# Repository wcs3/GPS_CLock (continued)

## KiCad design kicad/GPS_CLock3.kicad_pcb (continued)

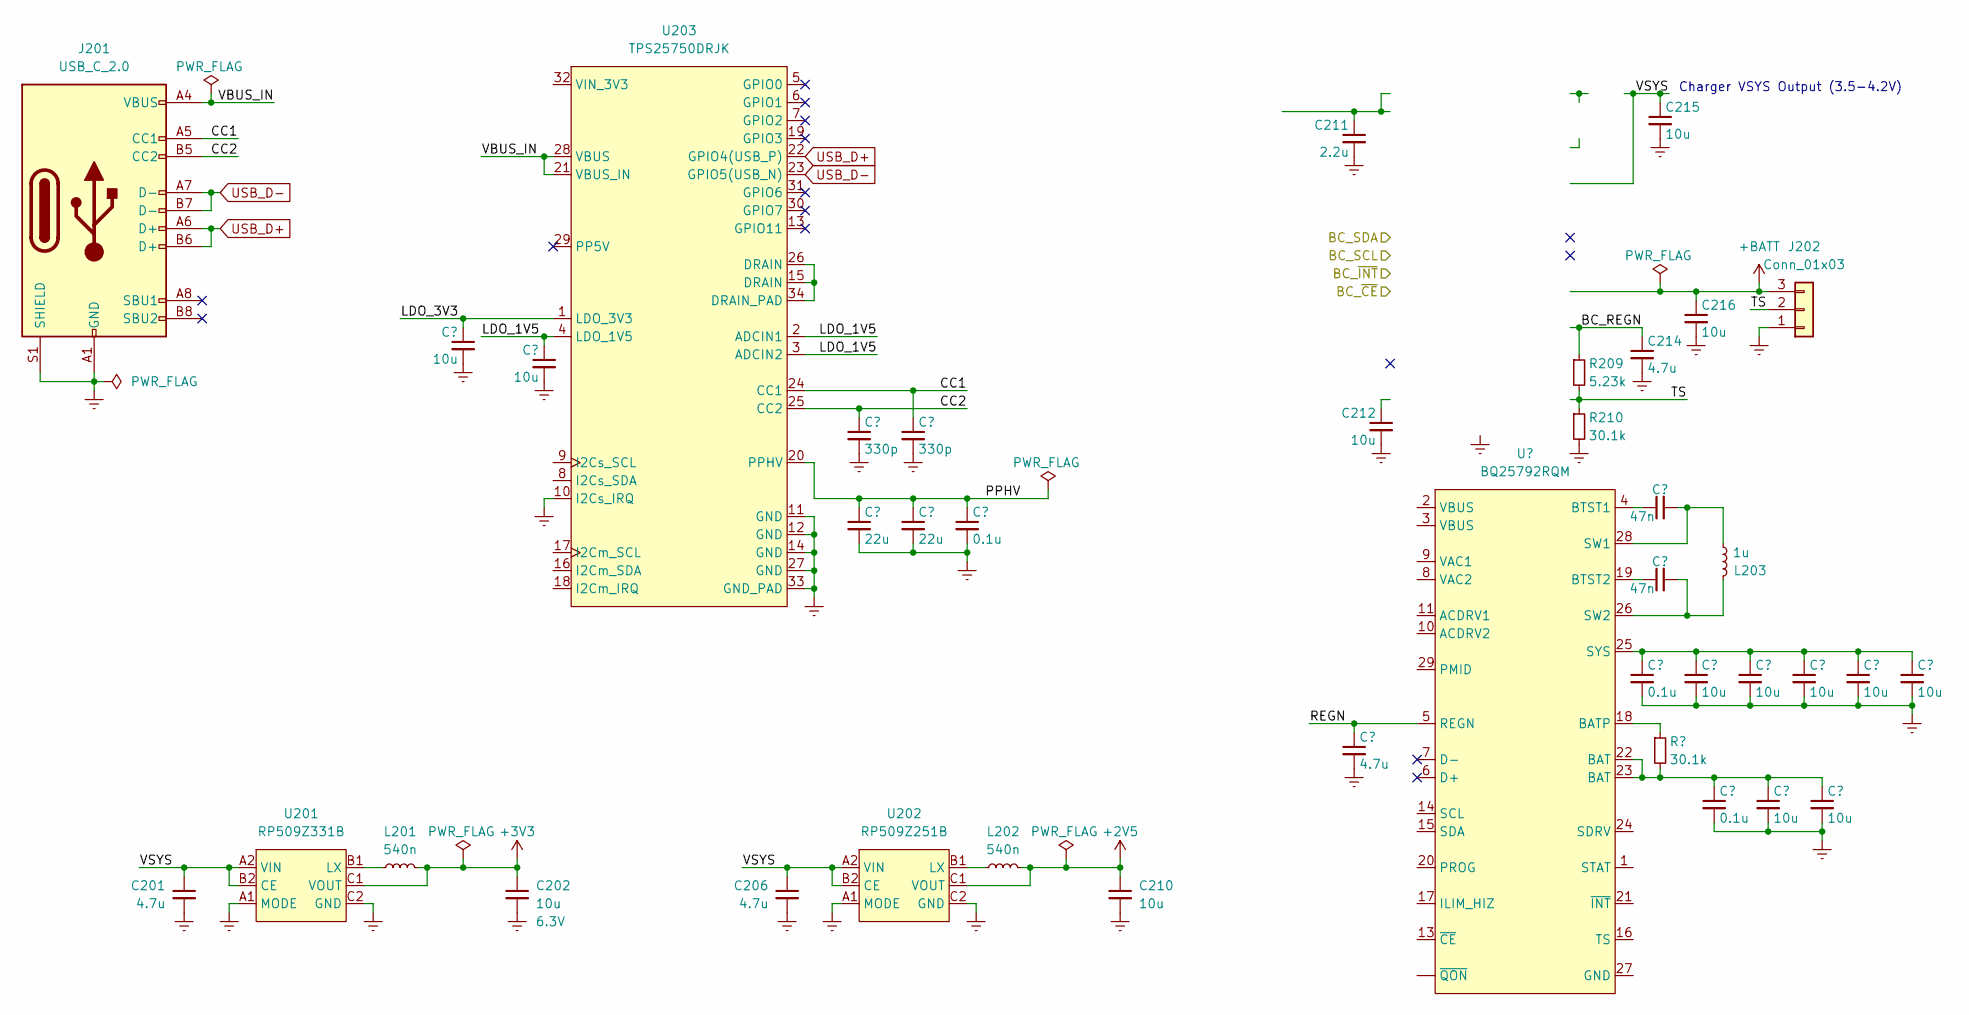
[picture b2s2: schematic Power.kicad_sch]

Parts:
C201, C206, C214: 4.7u; C_0402_1005Metric
C202: 10u; C_0402_1005Metric; Voltage 6.3V
C210, C212, C215, C216: 10u; C_0402_1005Metric
C211: 2.2u; C_0603_1608Metric
J201: USB_C_2.0; USB_C_Receptacle_JAE_DX07S016JA1R1500
J202: Conn_01x03; JST_XH_B3B-XH-A_1x03_P2.50mm_Vertical
L201, L202: 540n; L_0805_2012Metric
L203: 1u; Bourns_SRP2512
R209: 5.23k; R_0402_1005Metric
R210: 30.1k; R_0402_1005Metric
U201: RP509Z331B; WLCSP-6_1.4x1.0mm_P0.4mm
U202: RP509Z251B; WLCSP-6_1.4x1.0mm_P0.4mm
U203: TPS25750DRJK; POWERWQFN-40

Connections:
+2V5: C210.1, L202.2, U202.C1 (VOUT); also elsewhere on the board
+3V3: C202.1, L201.2, U201.C1 (VOUT); also elsewhere on the board
+BATT: C216.1, J202.3; also elsewhere on the board
/Power/BC_REGN: C214.1, R209.1; also elsewhere on the board
/Power/CC1: J201.A5 (CC1), U203.24 (CC1)
/Power/CC2: J201.B5 (CC2), U203.25 (CC2)
/Power/TS: J202.2, R209.2, R210.1; also elsewhere on the board
/Power/VBUS_IN: J201.A4 (VBUS), J201.A9 (VBUS), J201.B4 (VBUS), J201.B9 (VBUS), U203.21 (VBUS_IN), U203.28 (VBUS)
/Power/VBUS_OUT: C211.1; also elsewhere on the board
/Power/VSYS: C201.1, C206.1, C215.1, L203.2, U201.A2 (VIN), U201.B2 (CE), U202.A2 (VIN), U202.B2 (CE); also elsewhere on the board
Earth: C201.2, C202.2, C206.2, C210.2, C211.2, C212.2, C214.2, C215.2, C216.2, J201.A1 (GND), J201.A12 (GND), J201.B1 (GND), J201.B12 (GND), J201.S1 (SHIELD), J202.1, R210.2, U201.A1 (MODE), U201.C2 (GND), U202.A1 (MODE), U202.C2 (GND); also elsewhere on the board
unnamed 277: C212.1; also elsewhere on the board
unnamed 278: L203.1; also elsewhere on the board
unnamed: L201.1, U201.B1 (LX)
unnamed: L202.1, U202.B1 (LX)
USB_D+: J201.A6 (D+), J201.B6 (D+), U203.22 (GPIO4(USB_P)); also elsewhere on the board
USB_D-: J201.A7 (D-), J201.B7 (D-), U203.23 (GPIO5(USB_N)); also elsewhere on the board

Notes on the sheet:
Charger VSYS Output (3.5-4.2V)

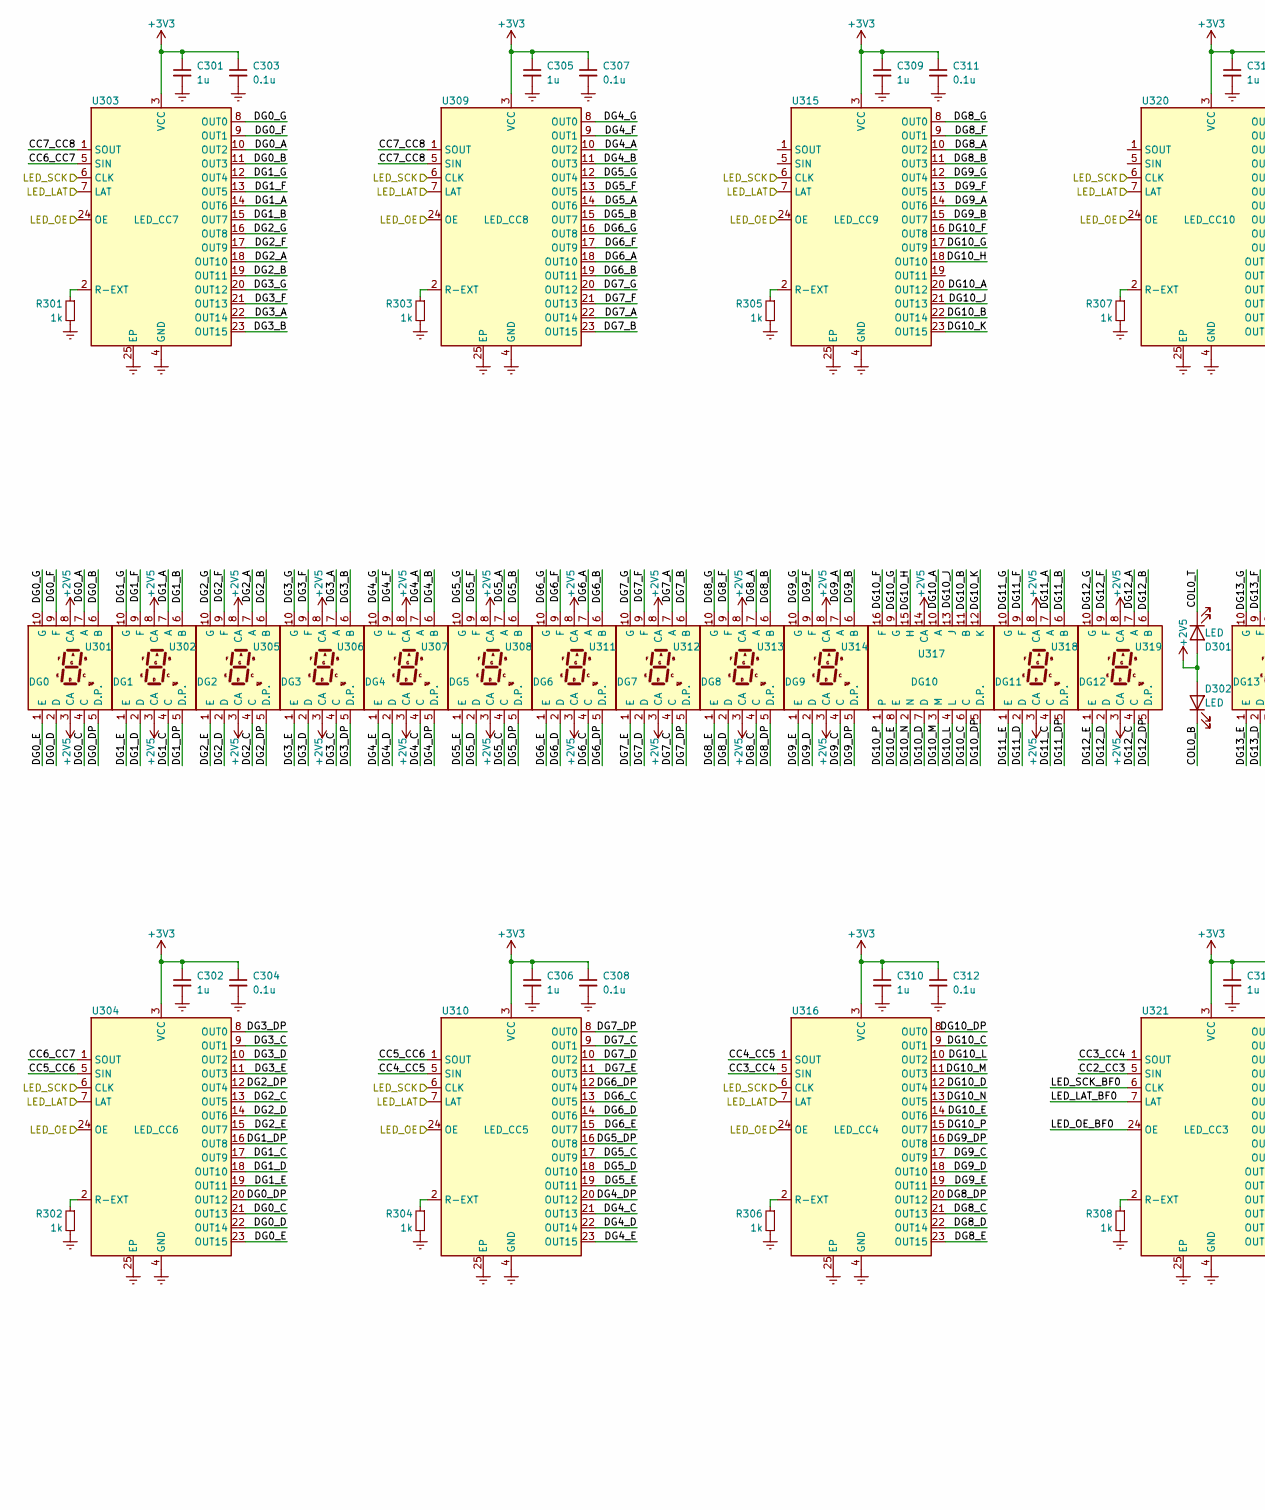
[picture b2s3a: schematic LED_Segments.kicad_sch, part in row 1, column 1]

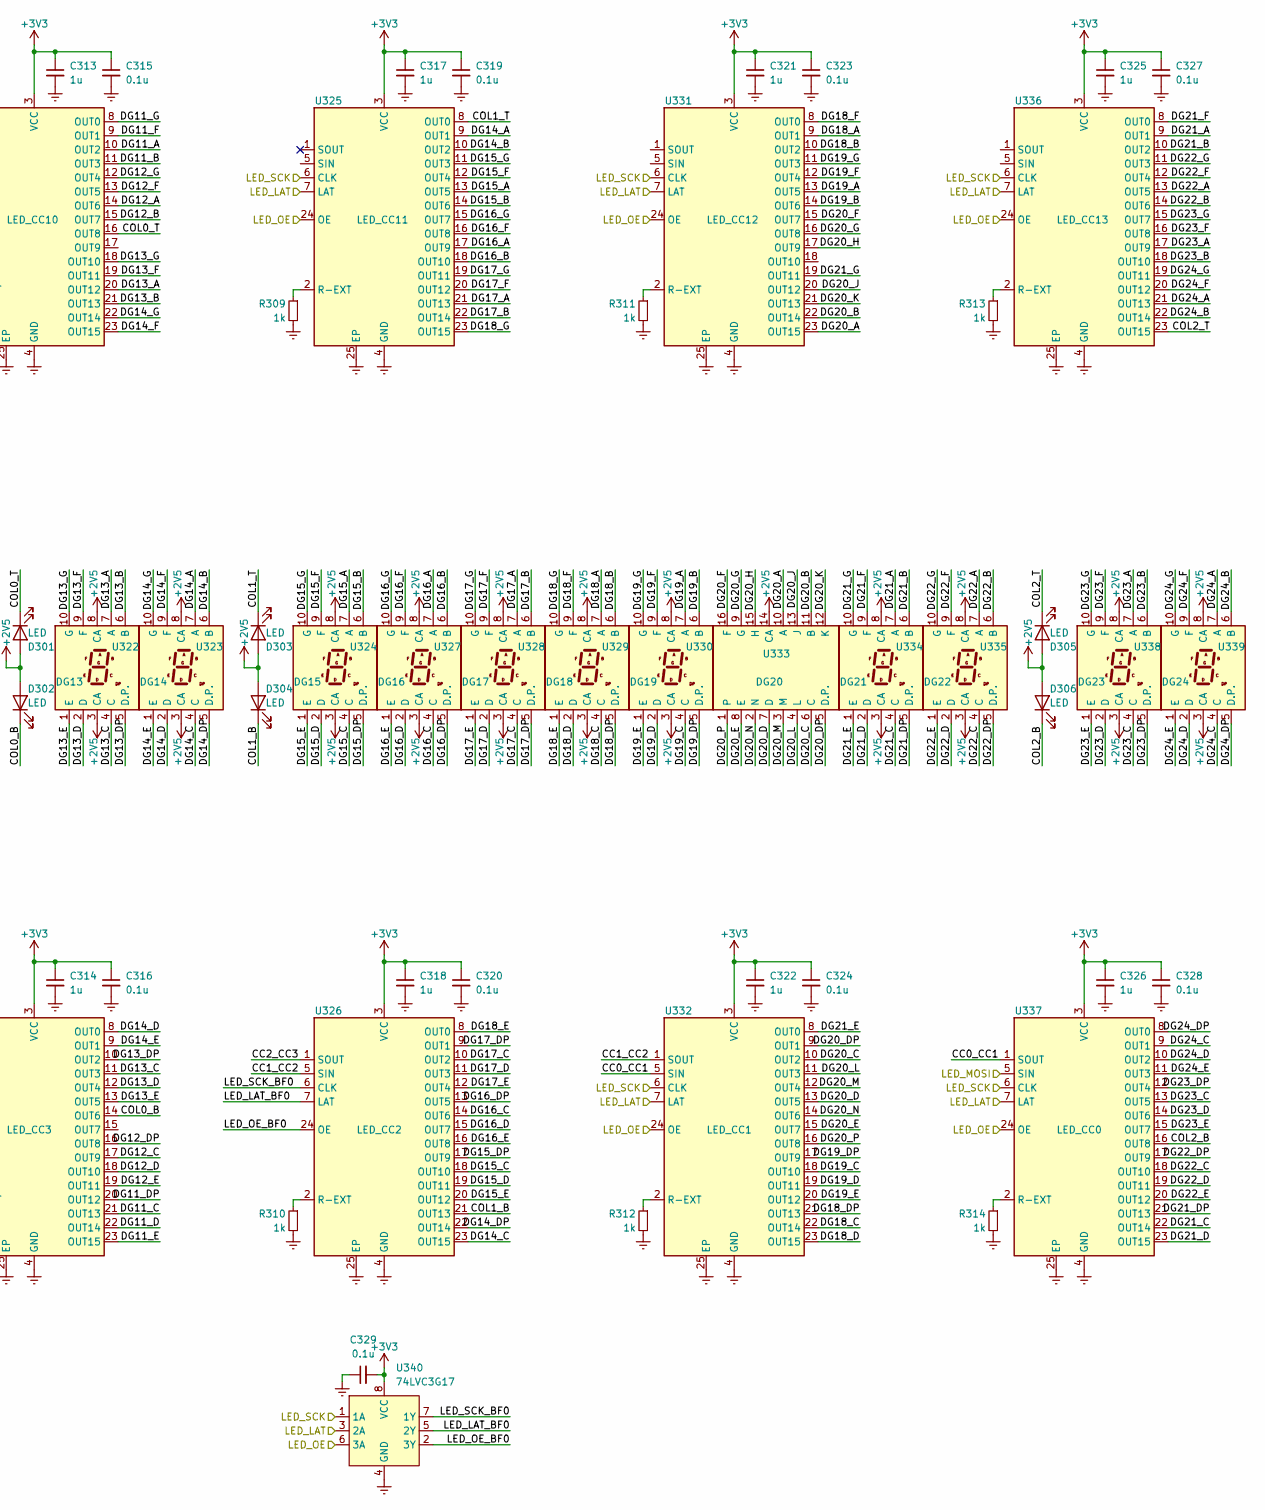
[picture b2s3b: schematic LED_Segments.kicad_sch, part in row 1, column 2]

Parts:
C301, C302, C305, C306, C309, C310, C313, C314, C317, C318, C321, C322, C325, C326: 1u; C_0402_1005Metric
C303, C304, C307, C308, C311, C312, C315, C316, C319, C320, C323, C324, C327, C328, C329: 0.1u; C_0402_1005Metric
D301, D302, D303, D304, D305, D306: LED; LED_0805_2012Metric
R301, R302, R303, R304, R305, R306, R307, R308, R309, R310, R311, R312, R313, R314: 1k; R_0402_1005Metric
U301: DG0; 7seg 0.56in smd
U302: DG1; 7seg 0.56in smd
U303: LED_CC7; QFN-24-1EP_4x4mm_P0.5mm_EP2.6x2.6mm
U304: LED_CC6; QFN-24-1EP_4x4mm_P0.5mm_EP2.6x2.6mm
U305: DG2; 7seg 0.56in smd
U306: DG3; 7seg 0.56in smd
U307: DG4; 7seg 0.56in smd
U308: DG5; 7seg 0.56in smd
U309: LED_CC8; QFN-24-1EP_4x4mm_P0.5mm_EP2.6x2.6mm
U310: LED_CC5; QFN-24-1EP_4x4mm_P0.5mm_EP2.6x2.6mm
U311: DG6; 7seg 0.56in smd
U312: DG7; 7seg 0.56in smd
U313: DG8; 7seg 0.56in smd
U314: DG9; 7seg 0.56in smd
U315: LED_CC9; QFN-24-1EP_4x4mm_P0.5mm_EP2.6x2.6mm
U316: LED_CC4; QFN-24-1EP_4x4mm_P0.5mm_EP2.6x2.6mm
U317: DG10; 14seg 0.4in smd
U318: DG11; 7seg 0.56in smd
U319: DG12; 7seg 0.56in smd
U320: LED_CC10; QFN-24-1EP_4x4mm_P0.5mm_EP2.6x2.6mm
U321: LED_CC3; QFN-24-1EP_4x4mm_P0.5mm_EP2.6x2.6mm
U322: DG13; 7seg 0.56in smd
U323: DG14; 7seg 0.56in smd
U324: DG15; 7seg 0.56in smd
U325: LED_CC11; QFN-24-1EP_4x4mm_P0.5mm_EP2.6x2.6mm
U326: LED_CC2; QFN-24-1EP_4x4mm_P0.5mm_EP2.6x2.6mm
U327: DG16; 7seg 0.56in smd
U328: DG17; 7seg 0.56in smd
U329: DG18; 7seg 0.56in smd
U330: DG19; 7seg 0.56in smd
U331: LED_CC12; QFN-24-1EP_4x4mm_P0.5mm_EP2.6x2.6mm
U332: LED_CC1; QFN-24-1EP_4x4mm_P0.5mm_EP2.6x2.6mm
U333: DG20; 14seg 0.4in smd
U334: DG21; 7seg 0.56in smd
U335: DG22; 7seg 0.56in smd
U336: LED_CC13; QFN-24-1EP_4x4mm_P0.5mm_EP2.6x2.6mm
U337: LED_CC0; QFN-24-1EP_4x4mm_P0.5mm_EP2.6x2.6mm
U338: DG23; 7seg 0.56in smd
U339: DG24; 7seg 0.56in smd
U340: 74LVC3G17; PSON50P100X195X50-8N

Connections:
+2V5: D301.2 (A), D302.2 (A), D303.2 (A), D304.2 (A), D305.2 (A), D306.2 (A), U301.3 (CA), U301.8 (CA), U302.3 (CA), U302.8 (CA), U305.3 (CA), U305.8 (CA), U306.3 (CA), U306.8 (CA), U307.3 (CA), U307.8 (CA), U308.3 (CA), U308.8 (CA), U311.3 (CA), U311.8 (CA), U312.3 (CA), U312.8 (CA), U313.3 (CA), U313.8 (CA), U314.3 (CA), U314.8 (CA), U317.14 (CA), U318.3 (CA), U318.8 (CA), U319.3 (CA), U319.8 (CA), U322.3 (CA), U322.8 (CA), U323.3 (CA), U323.8 (CA), U324.3 (CA), U324.8 (CA), U327.3 (CA), U327.8 (CA), U328.3 (CA), U328.8 (CA), U329.3 (CA), U329.8 (CA), U330.3 (CA), U330.8 (CA), U333.14 (CA), U334.3 (CA), U334.8 (CA), U335.3 (CA), U335.8 (CA), U338.3 (CA), U338.8 (CA), U339.3 (CA), U339.8 (CA); also elsewhere on the board
+3V3: C301.1, C302.1, C303.1, C304.1, C305.1, C306.1, C307.1, C308.1, C309.1, C310.1, C311.1, C312.1, C313.1, C314.1, C315.1, C316.1, C317.1, C318.1, C319.1, C320.1, C321.1, C322.1, C323.1, C324.1, C325.1, C326.1, C327.1, C328.1, C329.2, U303.3 (VCC), U304.3 (VCC), U309.3 (VCC), U310.3 (VCC), U315.3 (VCC), U316.3 (VCC), U320.3 (VCC), U321.3 (VCC), U325.3 (VCC), U326.3 (VCC), U331.3 (VCC), U332.3 (VCC), U336.3 (VCC), U337.3 (VCC), U340.8 (VCC); also elsewhere on the board
/LED_LAT: U303.7 (LAT), U304.7 (LAT), U309.7 (LAT), U310.7 (LAT), U315.7 (LAT), U316.7 (LAT), U320.7 (LAT), U325.7 (LAT), U331.7 (LAT), U332.7 (LAT), U336.7 (LAT), U337.7 (LAT), U340.3 (2A); also elsewhere on the board
/LED_MOSI: U337.5 (SIN); also elsewhere on the board
/LED_OE: U303.24 (OE), U304.24 (OE), U309.24 (OE), U310.24 (OE), U315.24 (OE), U316.24 (OE), U320.24 (OE), U325.24 (OE), U331.24 (OE), U332.24 (OE), U336.24 (OE), U337.24 (OE), U340.6 (3A); also elsewhere on the board
/LED_SCK: U303.6 (CLK), U304.6 (CLK), U309.6 (CLK), U310.6 (CLK), U315.6 (CLK), U316.6 (CLK), U320.6 (CLK), U325.6 (CLK), U331.6 (CLK), U332.6 (CLK), U336.6 (CLK), U337.6 (CLK), U340.1 (1A); also elsewhere on the board
/LED_Segments/CC0_CC1: U332.5 (SIN), U337.1 (SOUT)
/LED_Segments/CC1_CC2: U326.5 (SIN), U332.1 (SOUT)
/LED_Segments/CC2_CC3: U321.5 (SIN), U326.1 (SOUT)
/LED_Segments/CC3_CC4: U316.5 (SIN), U321.1 (SOUT)
/LED_Segments/CC4_CC5: U310.5 (SIN), U316.1 (SOUT)
/LED_Segments/CC5_CC6: U304.5 (SIN), U310.1 (SOUT)
/LED_Segments/CC6_CC7: U303.5 (SIN), U304.1 (SOUT)
/LED_Segments/CC7_CC8: U303.1 (SOUT), U309.1 (SOUT), U309.5 (SIN)
/LED_Segments/COL0_B: D302.1 (K), U321.14 (OUT6)
/LED_Segments/COL0_T: D301.1 (K), U320.16 (OUT8)
/LED_Segments/COL1_B: D304.1 (K), U326.21 (OUT13)
/LED_Segments/COL1_T: D303.1 (K), U325.8 (OUT0)
/LED_Segments/COL2_B: D306.1 (K), U337.16 (OUT8)
/LED_Segments/COL2_T: D305.1 (K), U336.23 (OUT15)
/LED_Segments/DG0_A: U301.7 (A), U303.10 (OUT2)
/LED_Segments/DG0_B: U301.6 (B), U303.11 (OUT3)
/LED_Segments/DG0_C: U301.4 (C), U304.21 (OUT13)
/LED_Segments/DG0_D: U301.2 (D), U304.22 (OUT14)
/LED_Segments/DG0_DP: U301.5 (D.P.), U304.20 (OUT12)
/LED_Segments/DG0_E: U301.1 (E), U304.23 (OUT15)
/LED_Segments/DG0_F: U301.9 (F), U303.9 (OUT1)
/LED_Segments/DG0_G: U301.10 (G), U303.8 (OUT0)
/LED_Segments/DG1_A: U302.7 (A), U303.14 (OUT6)
/LED_Segments/DG1_B: U302.6 (B), U303.15 (OUT7)
/LED_Segments/DG1_C: U302.4 (C), U304.17 (OUT9)
/LED_Segments/DG1_D: U302.2 (D), U304.18 (OUT10)
/LED_Segments/DG1_DP: U302.5 (D.P.), U304.16 (OUT8)
/LED_Segments/DG1_E: U302.1 (E), U304.19 (OUT11)
/LED_Segments/DG1_F: U302.9 (F), U303.13 (OUT5)
/LED_Segments/DG1_G: U302.10 (G), U303.12 (OUT4)
/LED_Segments/DG2_A: U303.18 (OUT10), U305.7 (A)
/LED_Segments/DG2_B: U303.19 (OUT11), U305.6 (B)
/LED_Segments/DG2_C: U304.13 (OUT5), U305.4 (C)
/LED_Segments/DG2_D: U304.14 (OUT6), U305.2 (D)
/LED_Segments/DG2_DP: U304.12 (OUT4), U305.5 (D.P.)
/LED_Segments/DG2_E: U304.15 (OUT7), U305.1 (E)
/LED_Segments/DG2_F: U303.17 (OUT9), U305.9 (F)
/LED_Segments/DG2_G: U303.16 (OUT8), U305.10 (G)
/LED_Segments/DG3_A: U303.22 (OUT14), U306.7 (A)
/LED_Segments/DG3_B: U303.23 (OUT15), U306.6 (B)
/LED_Segments/DG3_C: U304.9 (OUT1), U306.4 (C)
/LED_Segments/DG3_D: U304.10 (OUT2), U306.2 (D)
/LED_Segments/DG3_DP: U304.8 (OUT0), U306.5 (D.P.)
/LED_Segments/DG3_E: U304.11 (OUT3), U306.1 (E)
/LED_Segments/DG3_F: U303.21 (OUT13), U306.9 (F)
/LED_Segments/DG3_G: U303.20 (OUT12), U306.10 (G)
/LED_Segments/DG4_A: U307.7 (A), U309.10 (OUT2)
/LED_Segments/DG4_B: U307.6 (B), U309.11 (OUT3)
/LED_Segments/DG4_C: U307.4 (C), U310.21 (OUT13)
/LED_Segments/DG4_D: U307.2 (D), U310.22 (OUT14)
/LED_Segments/DG4_DP: U307.5 (D.P.), U310.20 (OUT12)
/LED_Segments/DG4_E: U307.1 (E), U310.23 (OUT15)
/LED_Segments/DG4_F: U307.9 (F), U309.9 (OUT1)
/LED_Segments/DG4_G: U307.10 (G), U309.8 (OUT0)
/LED_Segments/DG5_A: U308.7 (A), U309.14 (OUT6)
/LED_Segments/DG5_B: U308.6 (B), U309.15 (OUT7)
/LED_Segments/DG5_C: U308.4 (C), U310.17 (OUT9)
/LED_Segments/DG5_D: U308.2 (D), U310.18 (OUT10)
/LED_Segments/DG5_DP: U308.5 (D.P.), U310.16 (OUT8)
/LED_Segments/DG5_E: U308.1 (E), U310.19 (OUT11)
/LED_Segments/DG5_F: U308.9 (F), U309.13 (OUT5)
/LED_Segments/DG5_G: U308.10 (G), U309.12 (OUT4)
/LED_Segments/DG6_A: U309.18 (OUT10), U311.7 (A)
/LED_Segments/DG6_B: U309.19 (OUT11), U311.6 (B)
/LED_Segments/DG6_C: U310.13 (OUT5), U311.4 (C)
/LED_Segments/DG6_D: U310.14 (OUT6), U311.2 (D)
/LED_Segments/DG6_DP: U310.12 (OUT4), U311.5 (D.P.)
/LED_Segments/DG6_E: U310.15 (OUT7), U311.1 (E)
/LED_Segments/DG6_F: U309.17 (OUT9), U311.9 (F)
/LED_Segments/DG6_G: U309.16 (OUT8), U311.10 (G)
/LED_Segments/DG7_A: U309.22 (OUT14), U312.7 (A)
/LED_Segments/DG7_B: U309.23 (OUT15), U312.6 (B)
/LED_Segments/DG7_C: U310.9 (OUT1), U312.4 (C)
/LED_Segments/DG7_D: U310.10 (OUT2), U312.2 (D)
/LED_Segments/DG7_DP: U310.8 (OUT0), U312.5 (D.P.)
/LED_Segments/DG7_E: U310.11 (OUT3), U312.1 (E)
/LED_Segments/DG7_F: U309.21 (OUT13), U312.9 (F)
/LED_Segments/DG7_G: U309.20 (OUT12), U312.10 (G)
/LED_Segments/DG8_A: U313.7 (A), U315.10 (OUT2)
/LED_Segments/DG8_B: U313.6 (B), U315.11 (OUT3)
/LED_Segments/DG8_C: U313.4 (C), U316.21 (OUT13)
/LED_Segments/DG8_D: U313.2 (D), U316.22 (OUT14)
/LED_Segments/DG8_DP: U313.5 (D.P.), U316.20 (OUT12)
/LED_Segments/DG8_E: U313.1 (E), U316.23 (OUT15)
/LED_Segments/DG8_F: U313.9 (F), U315.9 (OUT1)
/LED_Segments/DG8_G: U313.10 (G), U315.8 (OUT0)
/LED_Segments/DG9_A: U314.7 (A), U315.14 (OUT6)
/LED_Segments/DG9_B: U314.6 (B), U315.15 (OUT7)
/LED_Segments/DG9_C: U314.4 (C), U316.17 (OUT9)
/LED_Segments/DG9_D: U314.2 (D), U316.18 (OUT10)
/LED_Segments/DG9_DP: U314.5 (D.P.), U316.16 (OUT8)
/LED_Segments/DG9_E: U314.1 (E), U316.19 (OUT11)
/LED_Segments/DG9_F: U314.9 (F), U315.13 (OUT5)
/LED_Segments/DG9_G: U314.10 (G), U315.12 (OUT4)
/LED_Segments/DG10_A: U315.20 (OUT12), U317.10 (A)
/LED_Segments/DG10_B: U315.22 (OUT14), U317.11 (B)
/LED_Segments/DG10_C: U316.9 (OUT1), U317.6 (C)
/LED_Segments/DG10_D: U316.12 (OUT4), U317.7 (D)
/LED_Segments/DG10_DP: U316.8 (OUT0), U317.5 (D.P.)
/LED_Segments/DG10_E: U316.14 (OUT6), U317.8 (E)
/LED_Segments/DG10_F: U315.16 (OUT8), U317.16 (F)
/LED_Segments/DG10_G: U315.17 (OUT9), U317.9 (G)
/LED_Segments/DG10_H: U315.18 (OUT10), U317.15 (H)
/LED_Segments/DG10_J: U315.21 (OUT13), U317.13 (J)
/LED_Segments/DG10_K: U315.23 (OUT15), U317.12 (K)
/LED_Segments/DG10_L: U316.10 (OUT2), U317.4 (L)
/LED_Segments/DG10_M: U316.11 (OUT3), U317.3 (M)
/LED_Segments/DG10_N: U316.13 (OUT5), U317.2 (N)
/LED_Segments/DG10_P: U316.15 (OUT7), U317.1
/LED_Segments/DG11_A: U318.7 (A), U320.10 (OUT2)
/LED_Segments/DG11_B: U318.6 (B), U320.11 (OUT3)
/LED_Segments/DG11_C: U318.4 (C), U321.21 (OUT13)
/LED_Segments/DG11_D: U318.2 (D), U321.22 (OUT14)
/LED_Segments/DG11_DP: U318.5 (D.P.), U321.20 (OUT12)
/LED_Segments/DG11_E: U318.1 (E), U321.23 (OUT15)
/LED_Segments/DG11_F: U318.9 (F), U320.9 (OUT1)
/LED_Segments/DG11_G: U318.10 (G), U320.8 (OUT0)
/LED_Segments/DG12_A: U319.7 (A), U320.14 (OUT6)
/LED_Segments/DG12_B: U319.6 (B), U320.15 (OUT7)
/LED_Segments/DG12_C: U319.4 (C), U321.17 (OUT9)
/LED_Segments/DG12_D: U319.2 (D), U321.18 (OUT10)
/LED_Segments/DG12_DP: U319.5 (D.P.), U321.16 (OUT8)
/LED_Segments/DG12_E: U319.1 (E), U321.19 (OUT11)
/LED_Segments/DG12_F: U319.9 (F), U320.13 (OUT5)
/LED_Segments/DG12_G: U319.10 (G), U320.12 (OUT4)
/LED_Segments/DG13_A: U320.20 (OUT12), U322.7 (A)
/LED_Segments/DG13_B: U320.21 (OUT13), U322.6 (B)
/LED_Segments/DG13_C: U321.11 (OUT3), U322.4 (C)
/LED_Segments/DG13_D: U321.12 (OUT4), U322.2 (D)
/LED_Segments/DG13_DP: U321.10 (OUT2), U322.5 (D.P.)
/LED_Segments/DG13_E: U321.13 (OUT5), U322.1 (E)
/LED_Segments/DG13_F: U320.19 (OUT11), U322.9 (F)
/LED_Segments/DG13_G: U320.18 (OUT10), U322.10 (G)
/LED_Segments/DG14_A: U323.7 (A), U325.9 (OUT1)
/LED_Segments/DG14_B: U323.6 (B), U325.10 (OUT2)
/LED_Segments/DG14_C: U323.4 (C), U326.23 (OUT15)
/LED_Segments/DG14_D: U321.8 (OUT0), U323.2 (D)
/LED_Segments/DG14_DP: U323.5 (D.P.), U326.22 (OUT14)
/LED_Segments/DG14_E: U321.9 (OUT1), U323.1 (E)
/LED_Segments/DG14_F: U320.23 (OUT15), U323.9 (F)
/LED_Segments/DG14_G: U320.22 (OUT14), U323.10 (G)
/LED_Segments/DG15_A: U324.7 (A), U325.13 (OUT5)
/LED_Segments/DG15_B: U324.6 (B), U325.14 (OUT6)
/LED_Segments/DG15_C: U324.4 (C), U326.18 (OUT10)
/LED_Segments/DG15_D: U324.2 (D), U326.19 (OUT11)
/LED_Segments/DG15_DP: U324.5 (D.P.), U326.17 (OUT9)
/LED_Segments/DG15_E: U324.1 (E), U326.20 (OUT12)
/LED_Segments/DG15_F: U324.9 (F), U325.12 (OUT4)
/LED_Segments/DG15_G: U324.10 (G), U325.11 (OUT3)
/LED_Segments/DG16_A: U325.17 (OUT9), U327.7 (A)
/LED_Segments/DG16_B: U325.18 (OUT10), U327.6 (B)
/LED_Segments/DG16_C: U326.14 (OUT6), U327.4 (C)
/LED_Segments/DG16_D: U326.15 (OUT7), U327.2 (D)
/LED_Segments/DG16_DP: U326.13 (OUT5), U327.5 (D.P.)
/LED_Segments/DG16_E: U326.16 (OUT8), U327.1 (E)
/LED_Segments/DG16_F: U325.16 (OUT8), U327.9 (F)
/LED_Segments/DG16_G: U325.15 (OUT7), U327.10 (G)
/LED_Segments/DG17_A: U325.21 (OUT13), U328.7 (A)
/LED_Segments/DG17_B: U325.22 (OUT14), U328.6 (B)
/LED_Segments/DG17_C: U326.10 (OUT2), U328.4 (C)
/LED_Segments/DG17_D: U326.11 (OUT3), U328.2 (D)
/LED_Segments/DG17_DP: U326.9 (OUT1), U328.5 (D.P.)
/LED_Segments/DG17_E: U326.12 (OUT4), U328.1 (E)
/LED_Segments/DG17_F: U325.20 (OUT12), U328.9 (F)
/LED_Segments/DG17_G: U325.19 (OUT11), U328.10 (G)
/LED_Segments/DG18_A: U329.7 (A), U331.9 (OUT1)
/LED_Segments/DG18_B: U329.6 (B), U331.10 (OUT2)
/LED_Segments/DG18_C: U329.4 (C), U332.22 (OUT14)
/LED_Segments/DG18_D: U329.2 (D), U332.23 (OUT15)
/LED_Segments/DG18_DP: U329.5 (D.P.), U332.21 (OUT13)
/LED_Segments/DG18_E: U326.8 (OUT0), U329.1 (E)
/LED_Segments/DG18_F: U329.9 (F), U331.8 (OUT0)
/LED_Segments/DG18_G: U325.23 (OUT15), U329.10 (G)
/LED_Segments/DG19_A: U330.7 (A), U331.13 (OUT5)
/LED_Segments/DG19_B: U330.6 (B), U331.14 (OUT6)
/LED_Segments/DG19_C: U330.4 (C), U332.18 (OUT10)
/LED_Segments/DG19_D: U330.2 (D), U332.19 (OUT11)
/LED_Segments/DG19_DP: U330.5 (D.P.), U332.17 (OUT9)
/LED_Segments/DG19_E: U330.1 (E), U332.20 (OUT12)
/LED_Segments/DG19_F: U330.9 (F), U331.12 (OUT4)
/LED_Segments/DG19_G: U330.10 (G), U331.11 (OUT3)
/LED_Segments/DG20_A: U331.23 (OUT15), U333.10 (A)
/LED_Segments/DG20_B: U331.22 (OUT14), U333.11 (B)
/LED_Segments/DG20_C: U332.10 (OUT2), U333.6 (C)
/LED_Segments/DG20_D: U332.13 (OUT5), U333.7 (D)
/LED_Segments/DG20_DP: U332.9 (OUT1), U333.5 (D.P.)
/LED_Segments/DG20_E: U332.15 (OUT7), U333.8 (E)
/LED_Segments/DG20_F: U331.15 (OUT7), U333.16 (F)
/LED_Segments/DG20_G: U331.16 (OUT8), U333.9 (G)
/LED_Segments/DG20_H: U331.17 (OUT9), U333.15 (H)
/LED_Segments/DG20_J: U331.20 (OUT12), U333.13 (J)
/LED_Segments/DG20_K: U331.21 (OUT13), U333.12 (K)
/LED_Segments/DG20_L: U332.11 (OUT3), U333.4 (L)
/LED_Segments/DG20_M: U332.12 (OUT4), U333.3 (M)
/LED_Segments/DG20_N: U332.14 (OUT6), U333.2 (N)
/LED_Segments/DG20_P: U332.16 (OUT8), U333.1
/LED_Segments/DG21_A: U334.7 (A), U336.9 (OUT1)
/LED_Segments/DG21_B: U334.6 (B), U336.10 (OUT2)
/LED_Segments/DG21_C: U334.4 (C), U337.22 (OUT14)
/LED_Segments/DG21_D: U334.2 (D), U337.23 (OUT15)
/LED_Segments/DG21_DP: U334.5 (D.P.), U337.21 (OUT13)
/LED_Segments/DG21_E: U332.8 (OUT0), U334.1 (E)
/LED_Segments/DG21_F: U334.9 (F), U336.8 (OUT0)
/LED_Segments/DG21_G: U331.19 (OUT11), U334.10 (G)
/LED_Segments/DG22_A: U335.7 (A), U336.13 (OUT5)
/LED_Segments/DG22_B: U335.6 (B), U336.14 (OUT6)
/LED_Segments/DG22_C: U335.4 (C), U337.18 (OUT10)
/LED_Segments/DG22_D: U335.2 (D), U337.19 (OUT11)
/LED_Segments/DG22_DP: U335.5 (D.P.), U337.17 (OUT9)
/LED_Segments/DG22_E: U335.1 (E), U337.20 (OUT12)
/LED_Segments/DG22_F: U335.9 (F), U336.12 (OUT4)
/LED_Segments/DG22_G: U335.10 (G), U336.11 (OUT3)
/LED_Segments/DG23_A: U336.17 (OUT9), U338.7 (A)
/LED_Segments/DG23_B: U336.18 (OUT10), U338.6 (B)
/LED_Segments/DG23_C: U337.13 (OUT5), U338.4 (C)
/LED_Segments/DG23_D: U337.14 (OUT6), U338.2 (D)
/LED_Segments/DG23_DP: U337.12 (OUT4), U338.5 (D.P.)
/LED_Segments/DG23_E: U337.15 (OUT7), U338.1 (E)
/LED_Segments/DG23_F: U336.16 (OUT8), U338.9 (F)
/LED_Segments/DG23_G: U336.15 (OUT7), U338.10 (G)
/LED_Segments/DG24_A: U336.21 (OUT13), U339.7 (A)
/LED_Segments/DG24_B: U336.22 (OUT14), U339.6 (B)
/LED_Segments/DG24_C: U337.9 (OUT1), U339.4 (C)
/LED_Segments/DG24_D: U337.10 (OUT2), U339.2 (D)
/LED_Segments/DG24_DP: U337.8 (OUT0), U339.5 (D.P.)
/LED_Segments/DG24_E: U337.11 (OUT3), U339.1 (E)
/LED_Segments/DG24_F: U336.20 (OUT12), U339.9 (F)
/LED_Segments/DG24_G: U336.19 (OUT11), U339.10 (G)
/LED_Segments/LED_LAT_BF0: U321.7 (LAT), U326.7 (LAT), U340.5 (2Y)
/LED_Segments/LED_OE_BF0: U321.24 (OE), U326.24 (OE), U340.2 (3Y)
/LED_Segments/LED_SCK_BF0: U321.6 (CLK), U326.6 (CLK), U340.7 (1Y)
Earth: C301.2, C302.2, C303.2, C304.2, C305.2, C306.2, C307.2, C308.2, C309.2, C310.2, C311.2, C312.2, C313.2, C314.2, C315.2, C316.2, C317.2, C318.2, C319.2, C320.2, C321.2, C322.2, C323.2, C324.2, C325.2, C326.2, C327.2, C328.2, C329.1, R301.2, R302.2, R303.2, R304.2, R305.2, R306.2, R307.2, R308.2, R309.2, R310.2, R311.2, R312.2, R313.2, R314.2, U303.4 (GND), U303.25 (EP), U304.4 (GND), U304.25 (EP), U309.4 (GND), U309.25 (EP), U310.4 (GND), U310.25 (EP), U315.4 (GND), U315.25 (EP), U316.4 (GND), U316.25 (EP), U320.4 (GND), U320.25 (EP), U321.4 (GND), U321.25 (EP), U325.4 (GND), U325.25 (EP), U326.4 (GND), U326.25 (EP), U331.4 (GND), U331.25 (EP), U332.4 (GND), U332.25 (EP), U336.4 (GND), U336.25 (EP), U337.4 (GND), U337.25 (EP), U340.4 (GND); also elsewhere on the board
unnamed: R301.1, U303.2 (R-EXT)
unnamed: R302.1, U304.2 (R-EXT)
unnamed: R303.1, U309.2 (R-EXT)
unnamed: R304.1, U310.2 (R-EXT)
unnamed: R305.1, U315.2 (R-EXT)
unnamed: R306.1, U316.2 (R-EXT)
unnamed: R307.1, U320.2 (R-EXT)
unnamed: R308.1, U321.2 (R-EXT)
unnamed: R309.1, U325.2 (R-EXT)
unnamed: R310.1, U326.2 (R-EXT)
unnamed: R311.1, U331.2 (R-EXT)
unnamed: R312.1, U332.2 (R-EXT)
unnamed: R313.1, U336.2 (R-EXT)
unnamed: R314.1, U337.2 (R-EXT)

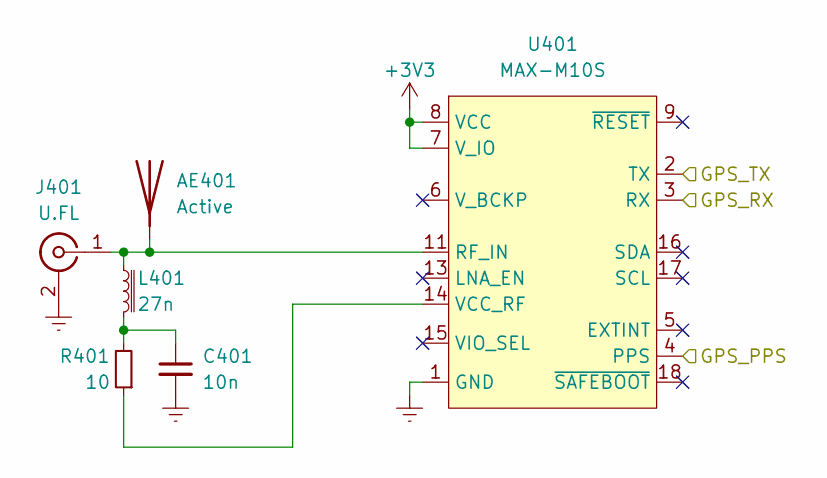
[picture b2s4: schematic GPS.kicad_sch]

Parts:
AE401: Active
C401: 10n; C_0402_1005Metric
J401: U.FL; U.FL_Hirose_U.FL-R-SMT-1_Vertical
L401: 27n; L_0402_1005Metric
R401: 10; R_0402_1005Metric
U401: MAX-M10S; UBLOX_MAX-M10S

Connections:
+3V3: U401.7 (V_IO), U401.8 (VCC); also elsewhere on the board
/GPS_PPS: U401.4 (PPS); also elsewhere on the board
/GPS_RX: U401.3 (RX); also elsewhere on the board
/GPS_TX: U401.2 (TX); also elsewhere on the board
Earth: C401.2, J401.2 (Ext), U401.1 (GND), U401.10 (GND), U401.12 (GND); also elsewhere on the board
unnamed: AE401.1, J401.1 (In), L401.1, U401.11 (RF_IN)
unnamed: C401.1, L401.2, R401.2
unnamed: R401.1, U401.14 (VCC_RF)

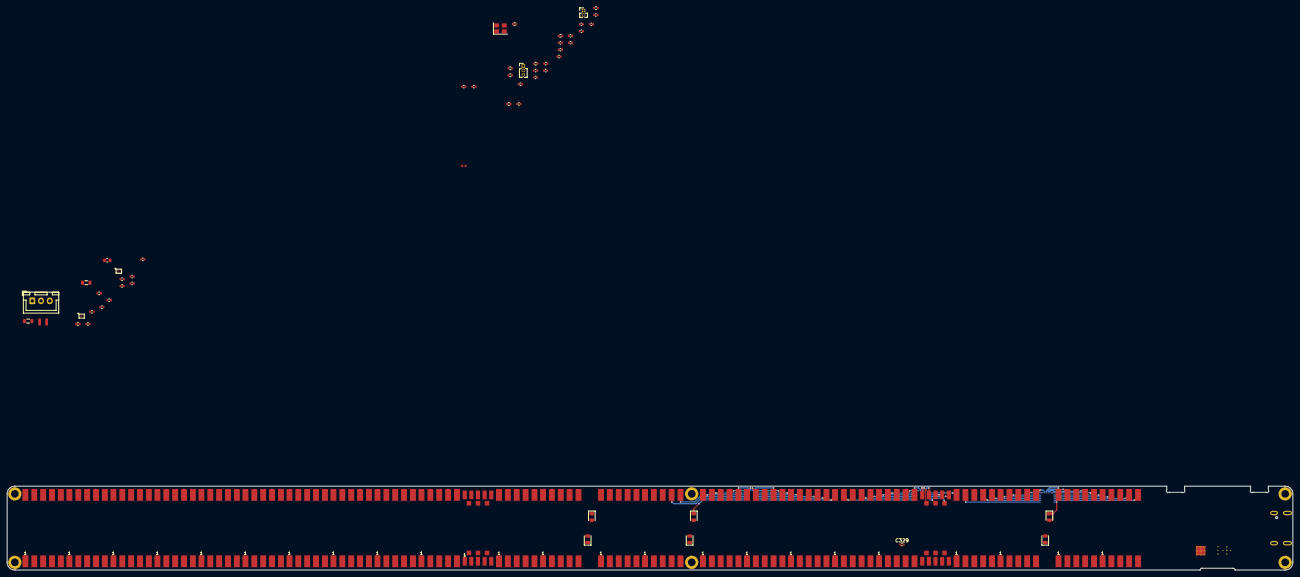
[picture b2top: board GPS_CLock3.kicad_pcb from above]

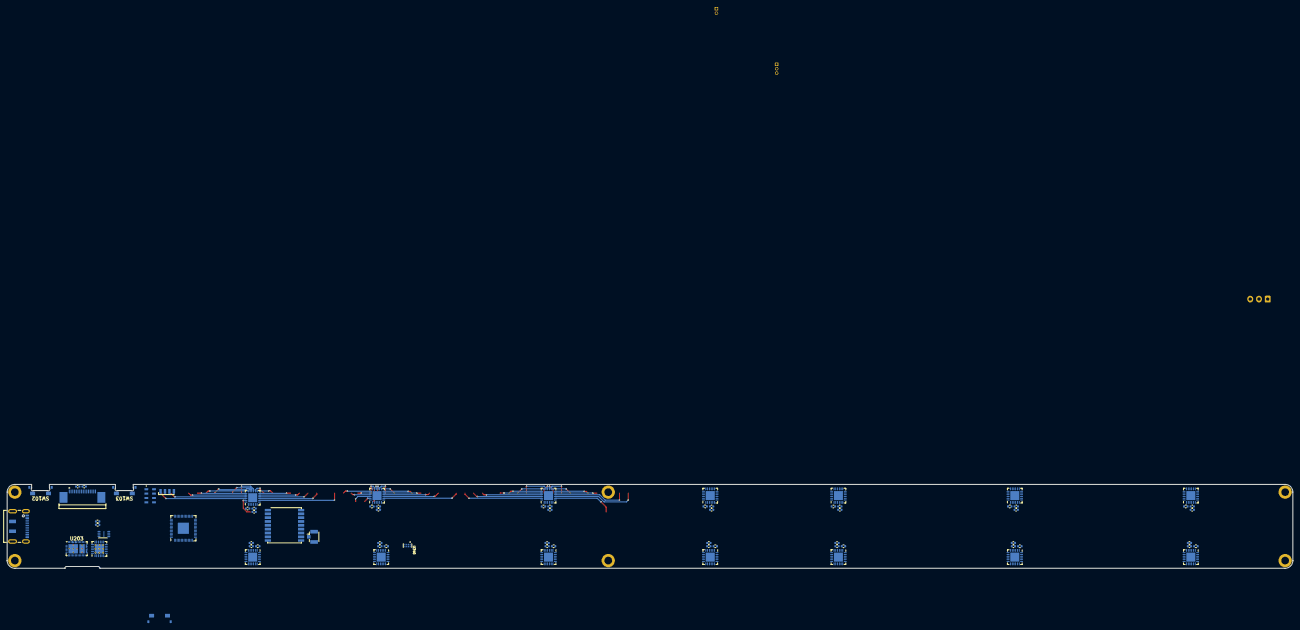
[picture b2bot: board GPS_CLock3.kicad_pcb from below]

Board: 4 copper layers, 368.1 x 24.0 mm, 158 parts (74 on the bottom side), 305 nets.

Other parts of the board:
C213: 47n; C_0402_1005Metric
C502, C503: 0.1u; C_0402_1005Metric
J501: 1-1734839-6; TE_1-1734839-6
U204: BQ25601; Texas_S-PWQFN-N24_EP2.7x2.7mm_ThermalVias

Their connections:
+3V3: J501.6, J501.7; also elsewhere on the board
+BATT: U204.13 (BAT), U204.14 (BAT); also elsewhere on the board
/BATT_EN: U204.9 (~CE); also elsewhere on the board
/OLED_CS: J501.8; also elsewhere on the board
/OLED_D/C: J501.10; also elsewhere on the board
/OLED_MOSI: J501.12; also elsewhere on the board
/OLED_RST: J501.9; also elsewhere on the board
/OLED_SCK: J501.11; also elsewhere on the board
/POW_SCL: U204.5 (SCL); also elsewhere on the board
/POW_SDA: U204.6 (SDA); also elsewhere on the board
/Power/BC_REGN: U204.2 (PSEL), U204.22 (REGN); also elsewhere on the board
/Power/TS: U204.11 (TS); also elsewhere on the board
/Power/VBUS_OUT: U204.1 (VAC), U204.24 (VBUS); also elsewhere on the board
/Power/VSYS: U204.15 (SYS), U204.16 (SYS); also elsewhere on the board
Earth: J501.4, J501.16, J501.S1 (SHIELD), J501.S2 (SHIELD), U204.17 (GND), U204.18 (GND), U204.25 (GND); also elsewhere on the board
unnamed 277: U204.23 (PMID); also elsewhere on the board
unnamed 278: C213.1, U204.19 (SW), U204.20 (SW); also elsewhere on the board
unnamed: C213.2, U204.21 (BTST)
unnamed: C502.1, J501.2
unnamed: C502.2, J501.1
unnamed: C503.1, J501.5
unnamed: C503.2, J501.3

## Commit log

2022-12-29 rename kicad project files
2022-12-29 update ignored files
2022-12-29 Update README.md
    flesh out feature list
2022-12-29 Update README.md
    add to feature list
2022-12-29 update pcb
2022-12-31 change to larger segments
2022-12-31 add schematic plot
2023-01-03 updated pcb
2023-01-10 add quickcharge 3.0 capability
2023-01-26 modify pcb
